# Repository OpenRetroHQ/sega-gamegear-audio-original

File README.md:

## Latest Schematic

## Latest 3d Rendering

## Latest PCB Layout

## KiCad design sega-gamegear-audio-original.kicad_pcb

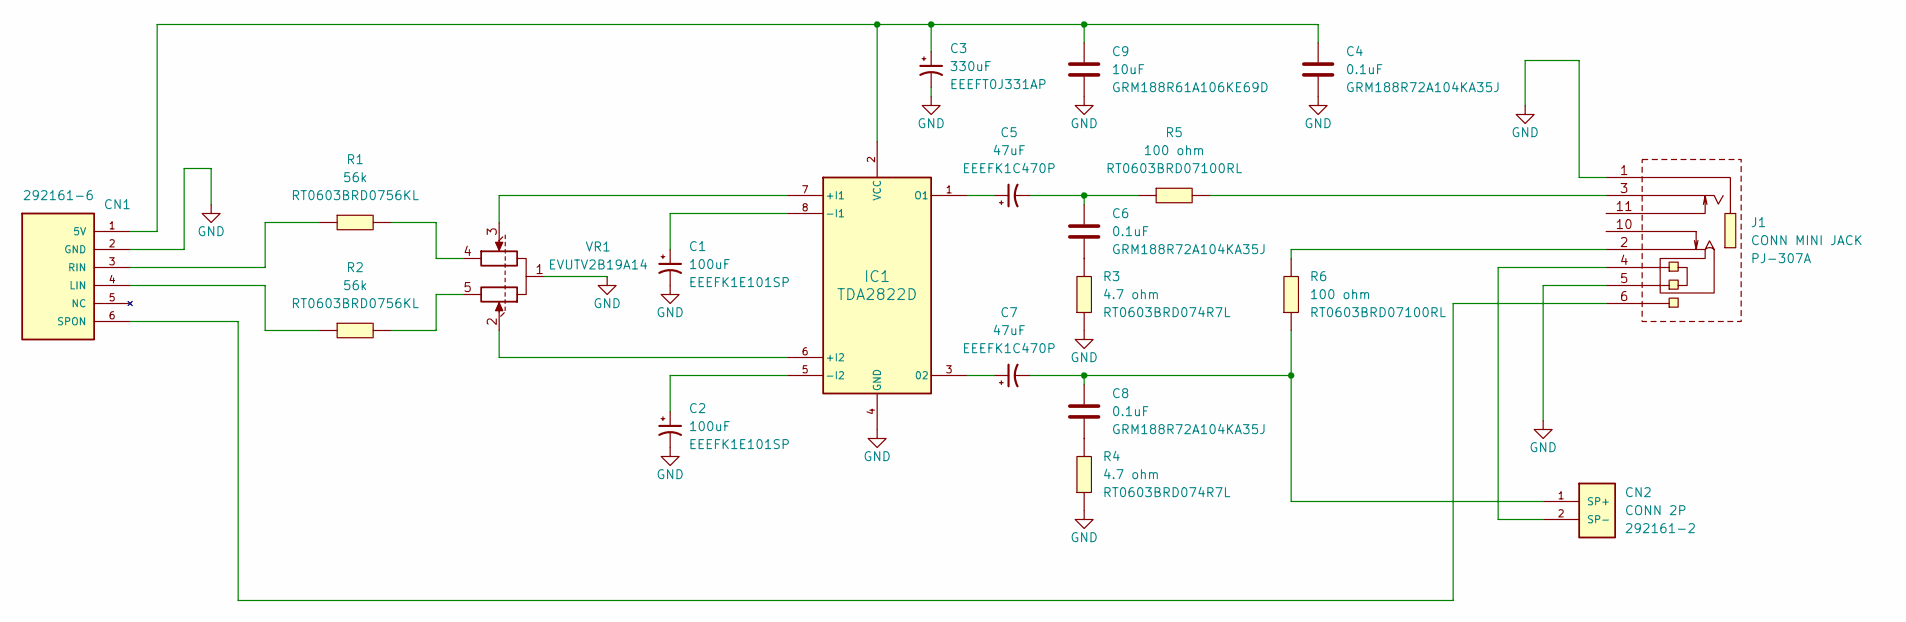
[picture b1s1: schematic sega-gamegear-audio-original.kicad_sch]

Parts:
C1, C2: 100uF; C63D; Manufacturer_Part_Number EEEFK1E101SP; LCSC Part C178540
C3: 330uF; C63D; Manufacturer_Part_Number EEEFT0J331AP; LCSC Part C178586
C4, C6, C8: 0.1uF; C0603; Manufacturer_Part_Number GRM188R72A104KA35J; LCSC Part C3011705
C5, C7: 47uF; C63D; Manufacturer_Part_Number EEEFK1C470P; LCSC Part C336261
C9: 10uF; C0603; Manufacturer_Part_Number GRM188R61A106KE69D; LCSC Part C77044
CN1: 292161-6; LCSC Part C499123
CN2: CONN 2P; 292161-2; Manufacturer_Part_Number 292161-2; LCSC Part C86484
IC1: TDA2822D; LCSC Part C668663
J1: CONN MINI JACK; PJ-307A; Manufacturer_Part_Number PJ-307A
R1, R2: 56k; R0603; Manufacturer_Part_Number RT0603BRD0756KL; LCSC Part C705785
R3, R4: 4.7 ohm; R0603; Manufacturer_Part_Number RT0603BRD074R7L; LCSC Part C861448
R5, R6: 100 ohm; R0603; Manufacturer_Part_Number RT0603BRD07100RL; LCSC Part C122970
VR1: EVUTV2B19A14

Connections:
GND: C1.2, C2.2, C3.2, C4.1, C9.1, CN1.2 (GND), IC1.4 (GND), J1.1, J1.5, R3.1, R4.1, VR1.1
unnamed: C5.2, C6.2, R5.1
unnamed: C6.1, R3.2
unnamed: C8.1, R4.2
unnamed: C3.1, C4.2, C9.2, CN1.1 (5V), IC1.2 (VCC)
unnamed: CN1.4 (LIN), R2.1
unnamed: CN1.3 (RIN), R1.1
unnamed: CN1.6 (SPON), J1.6
unnamed: C7.2, C8.2, CN2.1 (SP+), R6.1
unnamed: CN2.2 (SP-), J1.4
unnamed: C7.1, IC1.3 (02)
unnamed: IC1.7 (+I1), VR1.3
unnamed: IC1.6 (+I2), VR1.2
unnamed: C1.1, IC1.8 (-I1)
unnamed: C2.1, IC1.5 (-I2)
unnamed: C5.1, IC1.1 (O1)
unnamed: J1.2, R6.2
unnamed: J1.3, R5.2
unnamed: R1.2, VR1.4
unnamed: R2.2, VR1.5

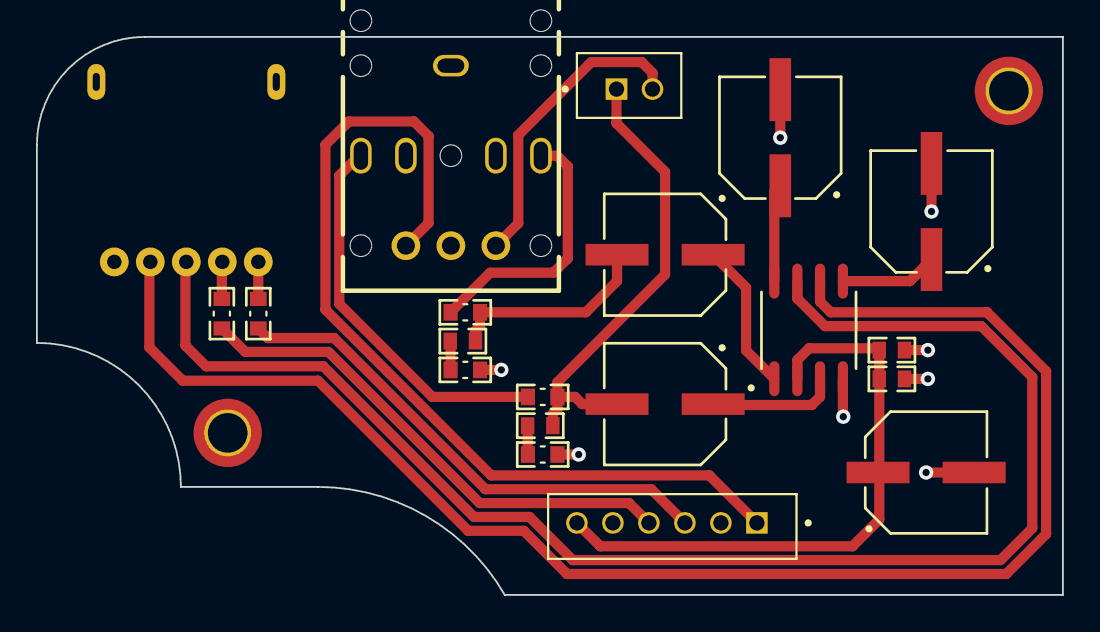
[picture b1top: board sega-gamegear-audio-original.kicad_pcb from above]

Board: 2 copper layers, 57.0 x 31.0 mm, 20 parts (0 on the bottom side), 20 nets.

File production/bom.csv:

Designator,Footprint,Quantity,Value,LCSC Part #
"C1, C2",C63D,2,100uF,C178540
C3,C63D,1,330uF,C178586
"C4, C6, C8",C0603,3,0.1uF,C3011705
"C5, C7",C63D,2,47uF,C336261
C9,C0603,1,10uF,C77044
CN1,292161-6,1,292161-6,C499123
CN2,292161-2,1,CONN 2P,C86484
IC1,TDA2822D,1,TDA2822D,C668663
J1,PJ-307A,1,CONN MINI JACK,
"R1, R2",R0603,2,56k,C705785
"R3, R4",R0603,2,4.7 ohm,C861448
"R5, R6",R0603,2,100 ohm,C122970
VR1,EVUTV2B19A14,1,EVUTV2B19A14,

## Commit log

2023-12-01 Add v1.2 screenshot
2023-12-03 add 1.3 screenshot
2023-12-10 initial schematics
2023-12-10 Add pdf
2023-12-11 update 3d models
2023-12-11 fix courtyards
2023-12-11 fix solder mask
2023-12-11 fix pj307a footprint
2023-12-11 add vr1 footprint
2023-12-11 add board outline
2023-12-11 add board settings for jlcpcb
2023-12-12 slightly better potentiometer 3d file
2023-12-12 add plated through holes
2023-12-12 Initial routing
2023-12-12 add vias
2023-12-12 trace sizing
2023-12-12 add board image
2023-12-12 update board export
2023-12-12 add 3d rendering
2023-12-12 add schematic
2023-12-12 upload pdf
2023-12-12 fixes #4 silkscreen issues
2023-12-12 fix drc
2023-12-12 add production files
2023-12-12 update production files
2023-12-13 update gitignore
2023-12-13 update sym table
2023-12-13 fix symbol spelling mistake
2023-12-13 swap out 100uf cap with legacy version for now
2023-12-13 update schematic screenshot
2023-12-13 fixes #6
2024-01-01 relocate volume wheel
2024-02-16 rerun production output
2024-02-21 hide silkscreen
2024-05-05 tweak wheel, headphone and mounting hole positions
2024-05-05 cleanup
2024-05-13 move mounting hole
2024-05-13 remove idea
2024-05-13 refab
